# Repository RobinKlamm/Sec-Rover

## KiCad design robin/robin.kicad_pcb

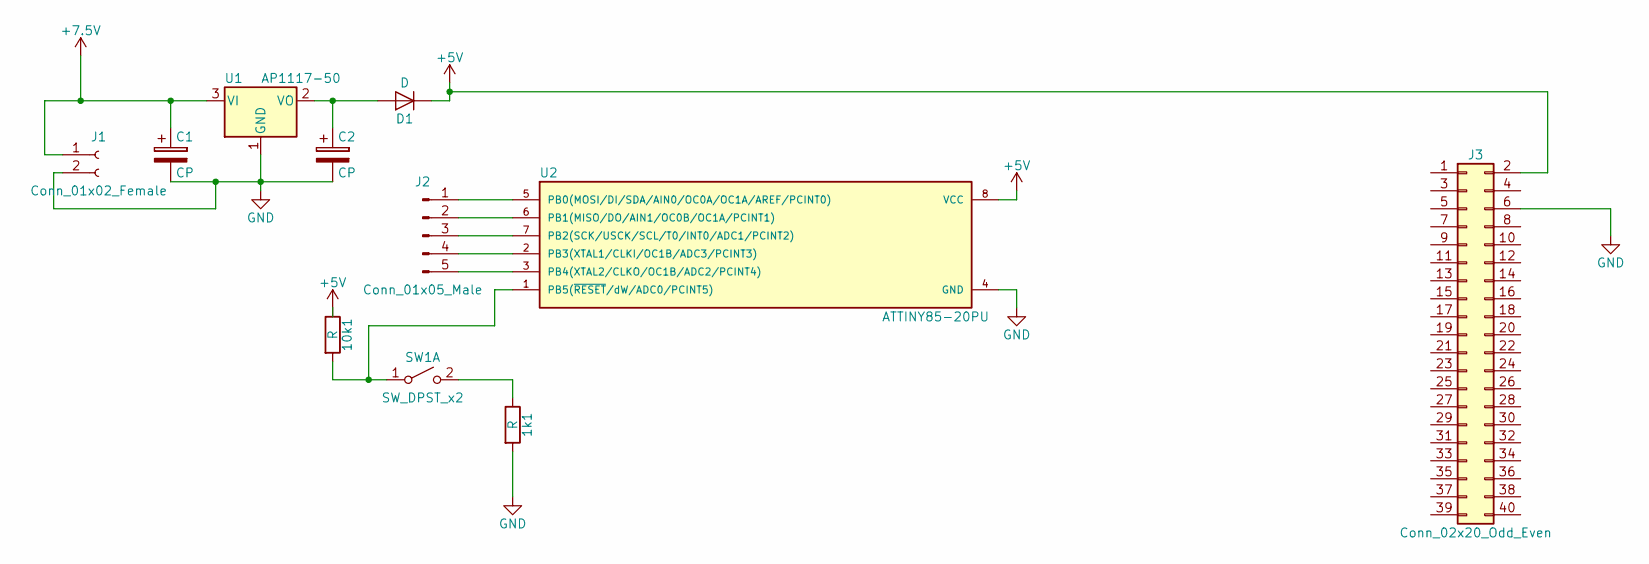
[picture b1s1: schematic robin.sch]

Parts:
1k1, 10k1: R; R_0805
C1, C2: CP; CP_Elec_4x4.5
D1: D; D_1206
J1: Conn_01x02_Female; Socket_Strip_Straight_1x02_Pitch2.54mm
J2: Conn_01x05_Male; Pin_Header_Straight_1x05_Pitch2.54mm
J3: Conn_02x20_Odd_Even; Socket_Strip_Straight_2x20_Pitch2.54mm
SW1: SW_DPST_x2; SW_PUSH_6mm
U1: AP1117-50; SOT-223-3_TabPin2
U2: ATTINY85-20PU; DIP-8_W10.16mm

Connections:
+5V: 10k1.1, D1.1 (K), J3.2, U2.8 (VCC)
+7.5V: C1.1, J1.1, U1.3 (VI)
GND: 1k1.2, C1.2, C2.2, J1.2, J3.6, U1.1 (GND), U2.4 (GND)
unnamed: 1k1.1, SW1.2 (B)
unnamed: 10k1.2, SW1.1 (A), U2.1 (PB5(~RESET~/dW/ADC0/PCINT5))
unnamed: C2.1, D1.2 (A), U1.2 (VO)
unnamed: J2.1, U2.5 (PB0(MOSI/DI/SDA/AIN0/OC0A/OC1A/AREF/PCI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)
unnamed: J2.2, U2.6 (PB1(MISO/DO/AIN1/OC0B/OC1A/PCINT1))
unnamed: J2.3, U2.7 (PB2(SCK/USCK/SCL/T0/INT0/ADC1/PCINT2))
unnamed: J2.4, U2.2 (PB3(XTAL1/CLKI/OC1B/ADC3/PCINT3))
unnamed: J2.5, U2.3 (PB4(XTAL2/CLKO/OC1B/ADC2/PCINT4))

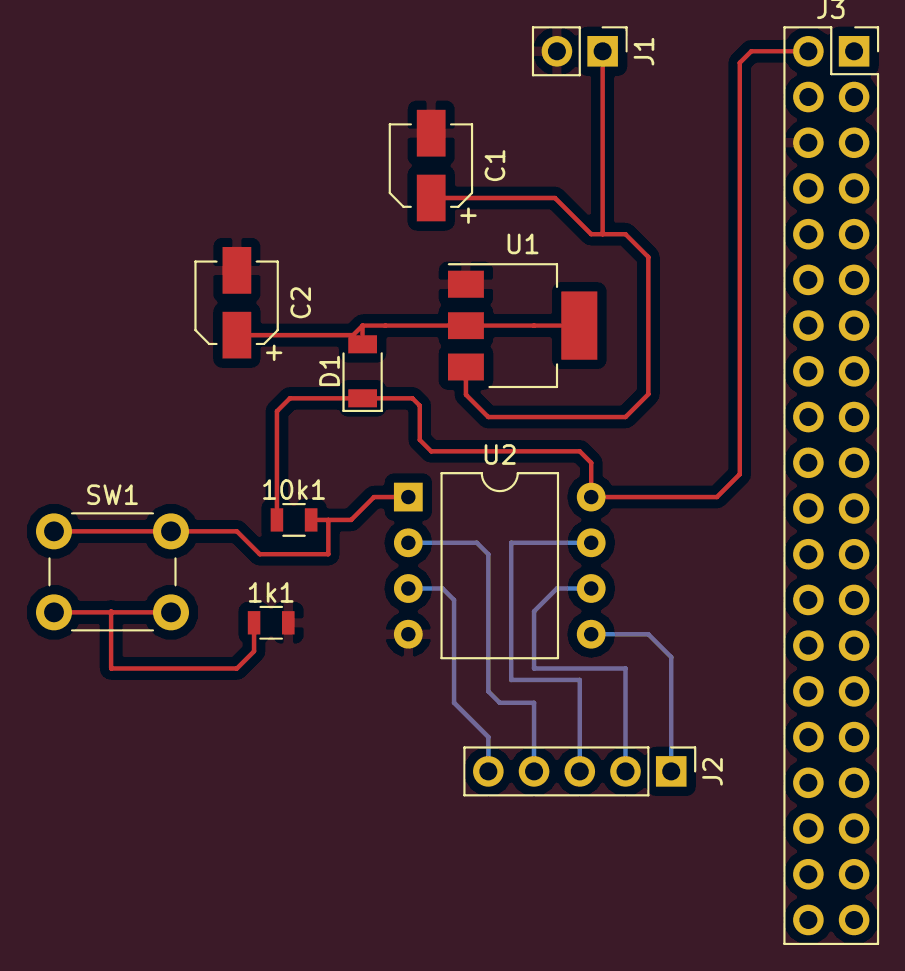
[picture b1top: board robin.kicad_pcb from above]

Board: 2 copper layers, 11 parts (0 on the bottom side), 11 nets.

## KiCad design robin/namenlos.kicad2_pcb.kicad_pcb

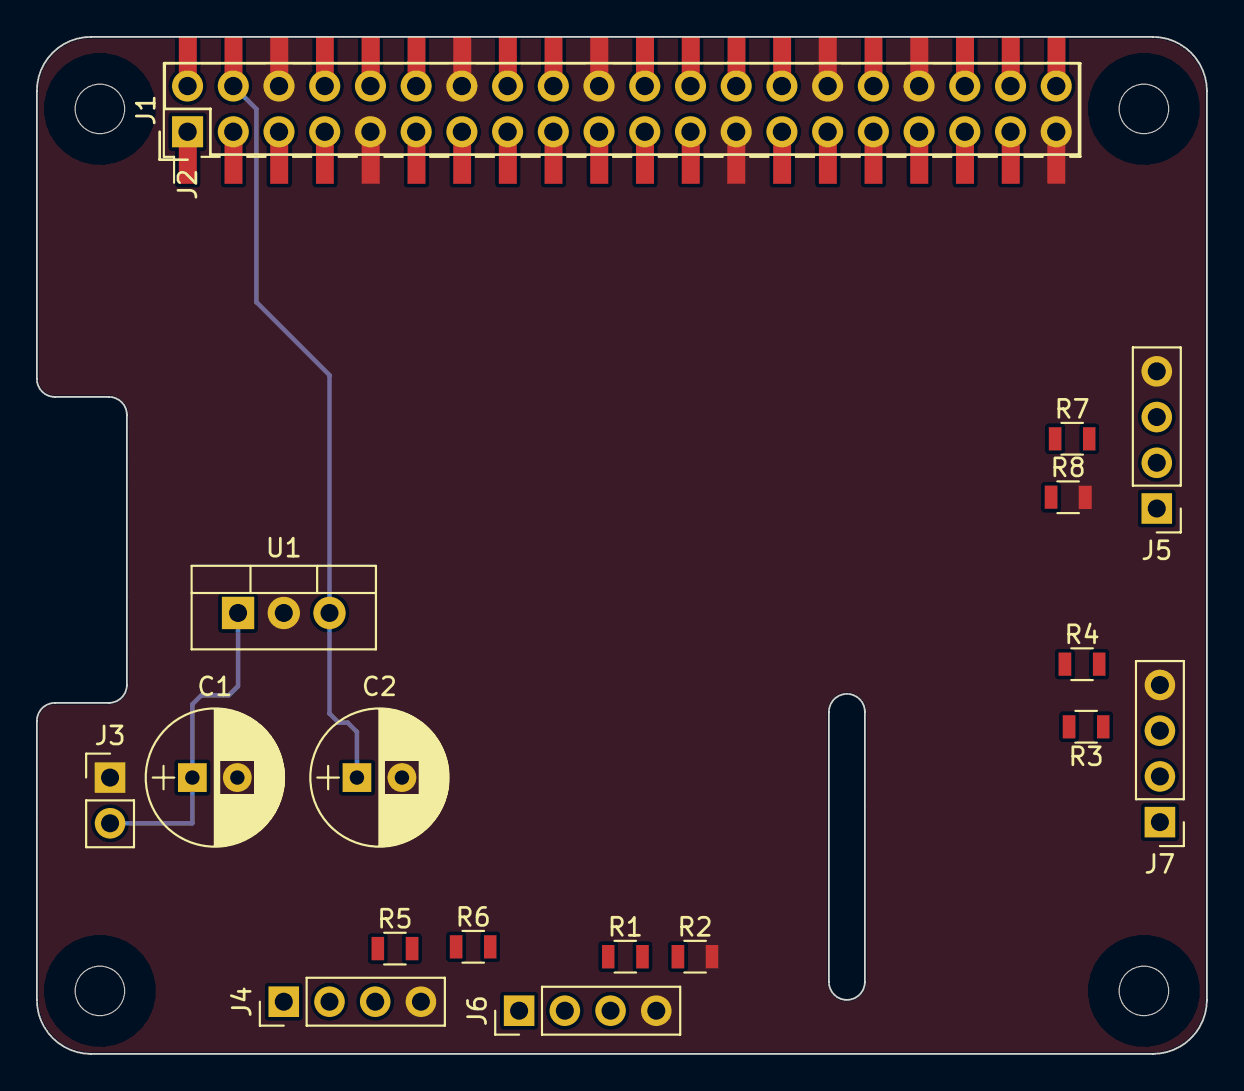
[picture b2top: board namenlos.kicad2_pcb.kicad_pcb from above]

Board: 2 copper layers, 65.0 x 56.5 mm, 18 parts (0 on the bottom side), 40 nets.

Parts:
C1, C2: CP; CP_Radial_D7.5mm_P2.50mm
J1: Conn_02x20_Odd_Even; Pin_Header_Straight_2x20_Pitch2.54mm_SMD
J2: RPi_GPIO; Pin_Header_Straight_2x20
J3: Conn_01x02_Female; Socket_Strip_Straight_1x02_Pitch2.54mm
J4, J5, J6, J7: Conn_01x04_Female; Socket_Strip_Straight_1x04_Pitch2.54mm
R1, R7: 330R; R_0805
R2, R8: 470R; R_0805
R3, R4, R5, R6: R; R_0805
U1: LM7805_TO220; TO-220-3_Vertical

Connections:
+3V3: J1.1, J1.17, J2.1, J2.17
+5V: C2.1, J1.2, J1.4, J2.2, J2.4, J4.1, J5.1, J6.1, J7.1, U1.3
+7.5V: C1.1, J3.2, U1.1
BCM0_ID_SD: J1.27, J2.27
BCM1_ID_SC: J1.28, J2.28
BCM2_SDA: J1.3, J2.3
BCM3_SCL: J1.5, J2.5
BCM4_GPCLK0: J1.7, J2.7
BCM5: J1.29, J2.29
BCM6: J1.31, J2.31
BCM7_CE1: J1.26, J2.26
BCM8_CE0: J1.24, J2.24
BCM9_MISO: J1.21, J2.21
BCM10_MOSI: J1.19, J2.19
BCM11_SCLK: J1.23, J2.23
BCM12: J1.32, J2.32
BCM13: J1.33, J2.33
BCM14_TXD: J1.8, J2.8
BCM15_RXD: J1.10, J2.10
BCM16: J1.36, J2.36
BCM17: J1.11, J2.11
BCM18_PCM_C: J1.12, J2.12
BCM19_MISO: J1.35, J2.35
BCM20_MOSI: J1.38, J2.38
BCM21_SCLK: J1.40, J2.40
BCM22: J1.15, J2.15
BCM23: J1.16, J2.16
BCM24: J1.18, J2.18
BCM25: J1.22, J2.22
BCM26: J1.37, J2.37
BCM27_PCM_D: J1.13, J2.13
ECHO_1: R1.2, R2.1
ECHO_2: R7.2, R8.1
ECHO_3: R3.2, R4.1
ECHO_4: R5.2, R6.1
GND: C1.2, C2.2, J1.6, J1.9, J1.14, J1.20, J1.25, J1.30, J1.34, J1.39, J2.6, J2.9, J2.14, J2.20, J2.25, J2.30, J2.34, J2.39, J3.1, J4.4, J5.4, J6.4, J7.4, R2.2, R8.2, U1.2
unnamed: J4.3, R5.1
unnamed: J5.3, R7.1
unnamed: J6.3, R1.1
unnamed: J7.3, R3.1

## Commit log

2018-07-26 CAD Dateien
    Das sin die CAD Dateien vom Laborcomputer
2018-07-26 Solid Works Dateien
    alle 3D Modelle aus Solid Works
2018-07-26 zeichnungen 2D
    Zeichnungen des Raspberry PI
